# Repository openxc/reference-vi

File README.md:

OpenXC Vehicle Interface Reference Design
=========================================

This repository is a part of the [OpenXC][] project.

This repository contains the documentation and open source design files for the
OpenXC vehicle interface reference design, originally created by Ford.

## Documentation

The documentation is in the form of simple website, written in Markdown with the
HTML generated with [Jekyll][jekyll].

[jekyll]: http://jekyllrb.com/

### Organization

* the `*.mkd` files are the source for the documentation website - they're very
  readable as plain text files, too, if you're just digging through the
  repository.
* `static/` contains the static JavaScript, CSS and images for the site.
* `_layouts/default.html` contains the main layout for the site. There's only 1
  layout for now, although there could others in the future.
* `electrical/` contains the electrical design files and documentation.
* `mechanical/` contains the mechanical housing design files and documentation.
* `assembly/` contains documentation to support final assembly at a fabrication
  house.

### Local development

If you do not have ruby and RubyGems installed (you already do on OS X), see
below.

Assuming you have Ruby and RubyGems installed:

    $ gem install rdiscount jekyll

Then, assuming you have Python's `pip` installed:

    $ pip install pygments

Then run the local development server:

    $ cd reference-vi
    reference-vi/ $ jekyll serve -w

and point your browser to http://localhost:4000.

Jekyll uses the templates in the repository to generate a static html version of
the site. The static version is always dumped in the `_site` subdirectory in the
repository - this is *not* committed, since it's automatically generated. The
`-w` flag turns on auto-recompilation, so anytime you change a file it will
regenerate whatever files have changed, so you just need to refresh the browser
to see your latest updates.

### Installing Ruby and RubyGems

**Cygwin in Windows**

TODO is this necessary anymore?

Install the `ruby`, `make`, `gcc`, `libiconv` and `zlib` packages in
Cygwin using the `setup.exe`
you downloaded earlier. Download the RubyGems TGZ package from
http://rubygems.org/pages/download and put it in `C:\cygwin\home\<your
username>`. Fire up Cygwin and run this:

    $ tar -xzf rubygems*.tgz
    $ cd rubygems*
    $ ruby setup.rb

Jekyll depends on posix-spawn v0.3.6, but that has a problem with compiling in
Cygwin. The latest development version works, though, so install that gem from
source before continuing:

    $ git clone https://github.com/rtomayko/posix-spawn.git
    $ cd posix-spawn
    $ gem build posix-spawn.gemspec
    $ gem install posix-spawn-0.3.6.gem

If you didn't get any errors, return to the top of this section and install
jekyll.

### Going Live

The documentation site is hosted on GitHub pages, so deploying is as simple as
commiting your changes to the `gh-pages` branch and pushing to GitHub. It gets
regenerated within a minute or two, and then it's live. This of course means
don't push anything in the `gh-pages` branch that isn't 100% done!

## License

Copyright (c) 2013 Ford Motor Company

The electrical and mechanical designs in this repository are available under the
[Creative Commons Attribution 4.0
International](http://creativecommons.org/licenses/by/4.0/deed.en_US) license.

[OpenXC]: http://openxcplatform.com

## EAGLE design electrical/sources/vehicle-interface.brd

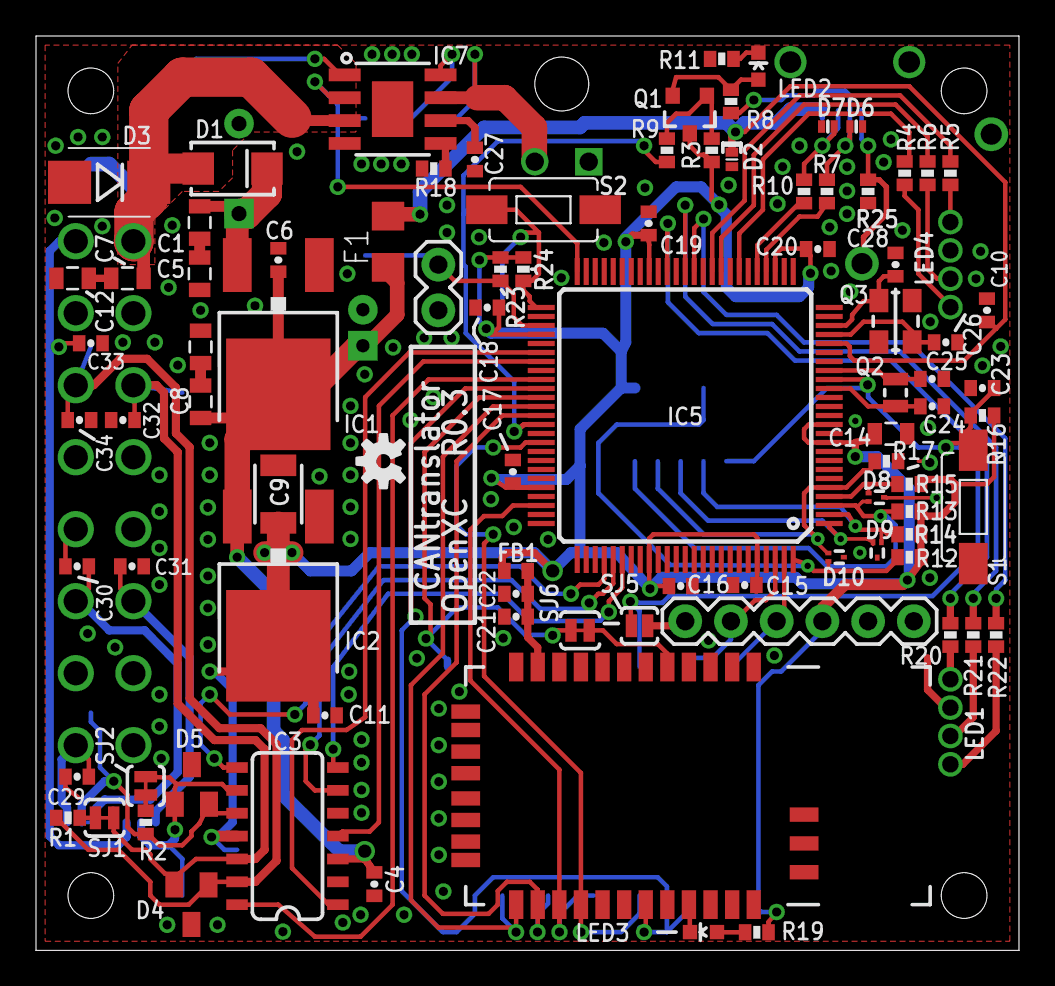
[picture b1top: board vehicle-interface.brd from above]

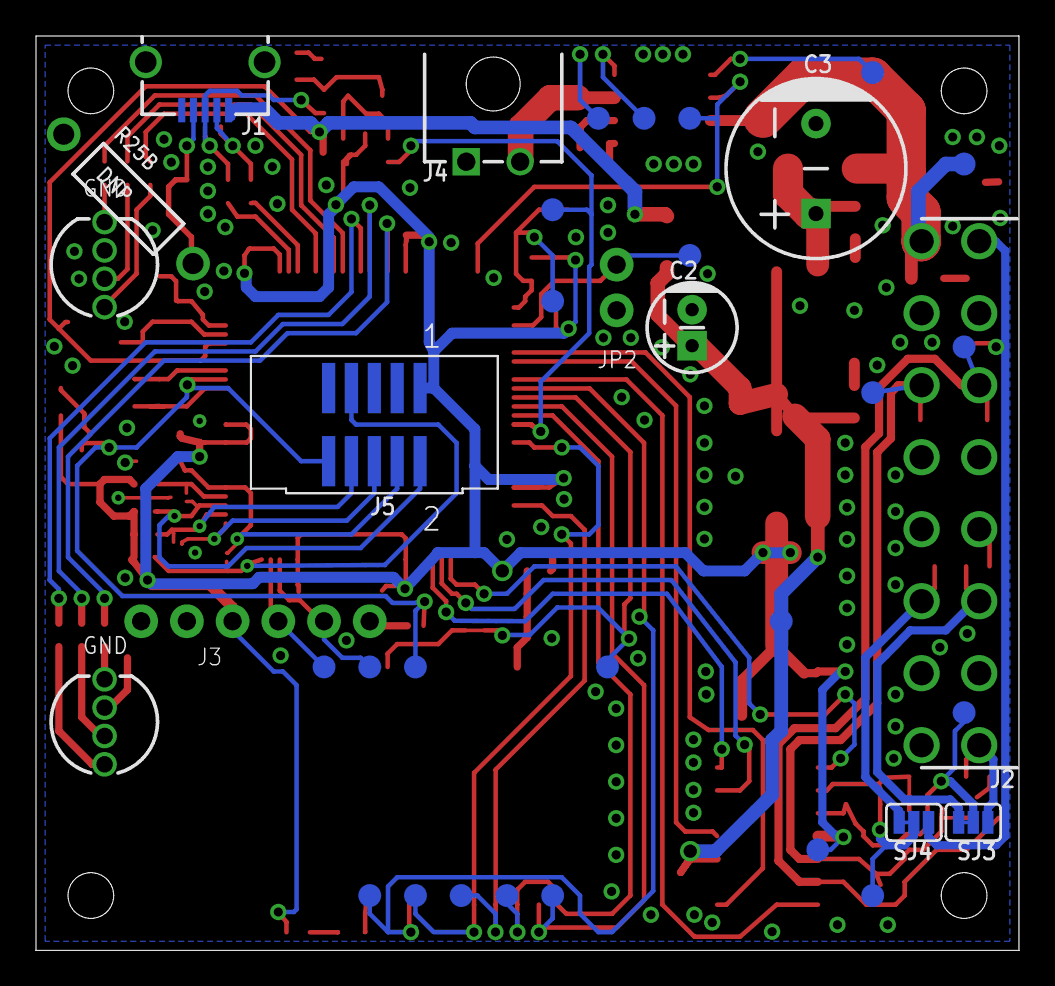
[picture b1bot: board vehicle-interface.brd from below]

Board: 2 copper layers, 54.6 x 50.8 mm, 125 parts (34 on the bottom side), 76 nets.

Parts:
C1, C5, C8, C13: 0.1u; 0805
C2: 150u; CPOL-5MMX2D
C3: 270u; CPOL-10MMX5D
C4, C11: 22n; 0402-CAP
C6, C10, C15, C16, C17, C18, C19, C20, C21, C23: 0.1u; 0402-CAP
C7, C12: 0.47u; 0805
C9: 47u; 1210
C14: 10u; 0805
C22, C27: 1u; 0402-CAP
C24, C25, C26, C28: 18p; 0402-CAP
C29, C30, C31, C32, C33, C34: 100p; 0402-CAP
D1: RS1J; SMA-DIODE
D2: PESD12VS1ULD; SOD-882D
D3: 1SMB16CAT3G; SMB-DIODE
D4, D5: PESD1CAN; SOT23
D6, D7: PESD5V0X1BL; SOD-882
D8, D9, D10: SOT-1123
DRILEGEND: DRILEGEND
F1: MF-MSMF110/16-2; R1206
F2: OSHW-LOGO-S
FB1: 742843122; C0402
IC1: LM340S-50; V-REG_DPACK
IC2: TLE4284DV33; V-REG_DPACK
IC3: TJA1048T; SO14
IC5: LPC1769FBD100; TQFP100
IC6: RN41-I/RM; RN41
IC7: TPS2421-2; POWER_SO8
J1: USB_MINIB_SHIELD-10118193; 10118193
J2: OBDII; OBDII-COMTECH
J3: ISP; 1X06
J4: PWR OUT; 2-1445055-2
J5: ARM mini-JTAG; SHF-105-01-X-D-SM
JP2: ISP_EN; 1X02
LED1, LED4: RGB; LED5MM-RGB
LED2, LED3: SML-LX0603SRW; LED-0603
Q1: BC856; SOT23-3
Q2: 32k; ST2012SB
Q3: 12M; CX3225SB
R1, R2, R25: 120; 0402-RES
R3, R12, R13, R14, R16, R17, R23, R24: 10k; 0402-RES
R4, R22: 17.4; 0402-RES
R5, R20: 143; 0402-RES
R6, R21: 30; 0402-RES
R7, R10: 33E; 0402-RES
R8: 1.5k; 0402-RES
R9: 2k; 0402-RES
R11, R19: 560; 0402-RES
R15: 4.7k; 0402-RES
R18: 49.9k; 0402-RES
R25B: DNP; AXIAL-0.4
S1: RESET; TACTILE-SWITCH-1101NE
S2: PROG; TACTILE-SWITCH-1101NE
SJ1, SJ2, SJ6: CLOSED; SJ_2S-TRACE
SJ3, SJ4: SJ_3_PASTE1&2
SJ5: OPEN; SJ_2S-NO
TP1, TP2, TP3, TP4, TP5, TP6, TP7, TP8, TP9, TP10, TP11, TP12, TP13, TP14, TP15, TP16, TP17, TP18, TP19, TP20, TP21, TP22, TP23: PAD.03X.05
ZDRAW1: A4L-LOC

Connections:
3.3V: C9.1, C11.1, C14.1, C15.1, C16.1, C17.1, C18.1, C19.1, C20.1, FB1.2, IC2.4, IC3.11, IC5.10, IC5.12, IC5.28, IC5.42, IC5.54, IC5.71, IC5.84, IC5.96, J3.4, J5.1, Q1.3, R3.2, R12.1, R13.1, R14.1, R15.1, R16.2, R19.1, R23.1, R24.1, TP7.P$1
5V: C2.1, C4.1, C6.2, C8.1, F1.1, IC1.4, IC2.3, IC3.3, TP6.P$1
!BT_RST: IC5.61, SJ6.1, TP12.P$1
!ISP_EN: IC5.53, JP2.1, R23.2, TP17.P$1
!RESET: C23.1, IC5.17, J5.10, R16.1, S1.P$2, SJ5.1, TP21.P$1
!USBBOOT_EN: IC5.51, R24.2, S2.P$2, TP18.P$1
+12V: C7.1, D1.A, D3.C, IC7.3, J2.16, TP5.P$1
BT_CONN: IC5.60, IC6.19, TP13.P$1
BT_CTS: IC5.66, IC6.16, TP11.P$1
BT_RTS: IC5.73, IC6.15, TP10.P$1
BT_RX: IC5.62, IC6.13, TP8.P$1
BT_TX: IC5.63, IC6.14, TP9.P$1
CANA_EN: IC3.14, IC5.59
CANA_RX: IC3.4, IC5.57
CANA_TX: IC3.1, IC5.56
CANB_EN: IC3.8, IC5.79
CANB_RX: IC3.7, IC5.81
CANB_TX: IC3.6, IC5.80
DEBUG_RX: IC5.99, J3.3, TP20.P$1
DEBUG_TX: IC5.98, J3.2, TP19.P$1
GND: C2.2, C3.1, C4.2, C5.2, C6.1, C9.2, C10.2, C11.2, C12.2, C13.2, C14.2, C15.2, C16.2, C17.2, C18.2, C19.2, C20.2, C21.1, C22.1, C23.2, C24.1, C25.1, C26.2, C27.2, C28.2, C29.2, C30.2, C31.2, C32.2, C33.2, C34.2, D2.2, D3.A, D4.3, D5.3, D6.1, D7.1, D8.3, D9.3, D10.3, IC1.1, IC2.1, IC3.2, IC3.5, IC5.11, IC5.15, IC5.31, IC5.41, IC5.55, IC5.72, IC5.83, IC5.97, IC6.1, IC6.12, IC6.25, IC6.27, IC6.28, IC6.29, IC7.4, IC7.PAD, J1.5, J1.S1, J1.S2, J2.4, J2.5, J3.6, J4.1, J5.3, J5.5, J5.9, JP2.2, LED1.2, LED4.2, R11.1, R17.2, R18.2, R25.1, R25B.P$1, S1.P$1, S2.P$1
HSPD_HI: C34.1, D4.1, IC3.13, J2.6, R1.1, TP1.P$1
HSPD_LO: C32.1, D4.2, IC3.12, J2.14, SJ1.1, TP2.P$1
MSPD_HI: C30.1, D5.2, IC3.10, J2.3, R2.2, SJ3.1, SJ3.2, TP3.P$1
MSPD_LO: C31.1, D5.1, IC3.9, J2.11, SJ2.2, SJ4.1, SJ4.2, TP4.P$1
MULTI_HI: C29.1, J2.1, SJ3.3
MULTI_LO: C33.1, J2.8, SJ4.3
unnamed: R1.2, SJ1.2
unnamed: IC5.40, R20.1
unnamed: R2.1, SJ2.1
unnamed: IC5.50, IC7.2, TP14.P$1
unnamed: LED1.4, R22.2
unnamed: IC6.21, LED3.C
unnamed: C7.2, C12.1
unnamed: LED3.A, R19.2
unnamed: IC5.38, R21.1
unnamed: IC5.37, R22.1
unnamed: LED1.3, R21.2
unnamed: LED1.1, R20.2
unnamed: IC7.5, R18.1
unnamed: C27.1, IC7.6
unnamed: LED4.4, R4.2
unnamed: IC5.32, R4.1
unnamed: C25.2, IC5.18, Q2.1
unnamed: C8.2, C13.1
unnamed: J1.4, R25.2, R25B.P$2
unnamed: D7.2, J1.2, R10.2
unnamed: C1.2, C5.1
unnamed: C1.1, C3.2, D1.C, IC1.3
unnamed: C24.2, IC5.16, Q2.2
unnamed: D6.2, J1.3, R7.2, R8.1
unnamed: C26.1, IC5.22, Q3.3
unnamed: C28.1, IC5.23, Q3.1
unnamed: LED2.A, Q1.2, R8.2
unnamed: LED2.C, R11.2
unnamed: Q1.1, R3.1, R9.1
unnamed: LED4.3, R6.2
unnamed: LED4.1, R5.2
unnamed: IC5.34, R6.1
unnamed: IC5.35, R5.1
unnamed: IC7.1, TP22.P$1
unnamed: IC7.8, TP23.P$1
unnamed: J3.1, SJ5.2
unnamed: IC6.5, SJ6.2
unnamed: C21.2, C22.2, FB1.1, IC6.11
RTCK: D10.2, IC5.100, J5.7, R12.2
TCK: D10.1, IC5.5, J5.4, R17.1
TDI: D9.1, IC5.2, J5.8, R14.2
TDO: D9.2, IC5.1, J5.6
TMS: D8.2, IC5.3, J5.2, R13.2
TRST: D8.1, IC5.4, R15.2
USB_CON: IC5.64, R9.2, TP16.P$1
USB_D+: IC5.29, R7.1
USB_D-: IC5.30, R10.1
USB_VBUS: C10.1, D2.1, F1.2, IC5.21, J1.1
VOUT: IC7.7, J4.2, TP15.P$1

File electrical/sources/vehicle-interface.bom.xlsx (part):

Part | Value | Package | Manu | Part # | Volt/Precision | Other | Link | Cost/1k
C1 | 0.1u | CAP0805 | Kemet | C0805C104K5RACAUTO | X7R | 50V | http://ca.mouser.com/ProductDetail/Kemet/C0805C104K5RACAUTO/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 | 2.7E-2
C2 | 150u | CAP_POL5MMX2D | Panasonic | EEU-FR1A151B | 0.2 | 10V | http://ca.mouser.com/ProductDetail/Panasonic-Electronic-Comp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 | 6.4000000000000001E-2
C3 | 270u | CAP_POL10MMX5D | Panasonic | EEU-FR1V271 | 0.2 | 35V | http://www.digikey.com/product-detail/en/EEU-FR1V271/P14438-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 | 0.214
C4 | 22n | CAP0402-CAP | Murata | GCM155R71H223KA55D | X7R | 16V | http://ca.mouser.com/ProductDetail/Murata/GCM155R71H223KA55D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 | 1.6E-2 |  | Change to 0603 package
C5 | 0.1u | CAP0805 | Kemet | C0805C104K5RACAUTO | X7R | 50V | http://ca.mouser.com/ProductDetail/Kemet/C0805C104K5RACAUTO/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 | 2.7E-2
C6 | 0.1u | CAP0402-CAP | Murata | GRM155R71C104JA88D | X7R | 16V | http://ca.mouser.com/ProductDetail/Murata/GRM155R71C104JA88D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 | 7.0000000000000001E-3 |  | Change to 0603 package
C7 | 0.47u | CAP0805 | Kemet | C0805C474K5RACTU | X7R | 50V | http://ca.mouser.com/ProductDetail/Kemet/C0805C474K5RACTU/?q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 | 6.3E-2
C8 | 0.1u | CAP0805 | Kemet | C0805C104K5RACAUTO | X7R | 50V | http://ca.mouser.com/ProductDetail/Kemet/C0805C104K5RACAUTO/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 | 2.7E-2
C9 | 47u | CAP1210 | Murata | GRM32ER71A476KE15L | X7R | 10V | http://ca.mouser.com/ProductDetail/Murata/GRM32ER71A476KE15L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 | 0.72199999999999998
C10 | 0.1u | CAP0402-CAP | Murata | GRM155R71C104JA88D | X7R | 16V | http://ca.mouser.com/ProductDetail/Murata/GRM155R71C104JA88D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 | 7.0000000000000001E-3 |  | Change to 0603 package
C11 | 22n | CAP0402-CAP | Murata | GCM155R71H223KA55D | X7R | 16V | http://ca.mouser.com/ProductDetail/Murata/GCM155R71H223KA55D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 | 1.6E-2 |  | Change to 0603 package
C12 | 0.47u | CAP0805 | Kemet | C0805C474K5RACTU | X7R | 50V | http://ca.mouser.com/ProductDetail/Kemet/C0805C474K5RACTU/?q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 | 6.3E-2
C13 | 0.1u | CAP0805 | Kemet | C0805C104K5RACAUTO | X7R | 50V | http://ca.mouser.com/ProductDetail/Kemet/C0805C104K5RACAUTO/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 | 2.7E-2
C14 | 10u | CAP0805 | Kemet | C0805C106K8RACTU | X7R | 10V | http://ca.mouser.com/ProductDetail/Kemet/C0805C106K8RACTU/?q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 | 0.14799999999999999
C15 | 0.1u | CAP0402-CAP | Murata | GRM155R71C104JA88D | X7R | 16V | http://ca.mouser.com/ProductDetail/Murata/GRM155R71C104JA88D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 | 7.0000000000000001E-3 |  | Change to 0603 package
C16 | 0.1u | CAP0402-CAP | Murata | GRM155R71C104JA88D | X7R | 16V | http://ca.mouser.com/ProductDetail/Murata/GRM155R71C104JA88D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 | 7.0000000000000001E-3 |  | Change to 0603 package
C17 | 0.1u | CAP0402-CAP | Murata | GRM155R71C104JA88D | X7R | 16V | http://ca.mouser.com/ProductDetail/Murata/GRM155R71C104JA88D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 | 7.0000000000000001E-3 |  | Change to 0603 package
C18 | 0.1u | CAP0402-CAP | Murata | GRM155R71C104JA88D | X7R | 16V | http://ca.mouser.com/ProductDetail/Murata/GRM155R71C104JA88D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 | 7.0000000000000001E-3 |  | Change to 0603 package
C19 | 0.1u | CAP0402-CAP | Murata | GRM155R71C104JA88D | X7R | 16V | http://ca.mouser.com/ProductDetail/Murata/GRM155R71C104JA88D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 | 7.0000000000000001E-3 |  | Change to 0603 package
C20 | 0.1u | CAP0402-CAP | Murata | GRM155R71C104JA88D | X7R | 16V | http://ca.mouser.com/ProductDetail/Murata/GRM155R71C104JA88D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 | 7.0000000000000001E-3 |  | Change to 0603 package
C21 | 0.1u | CAP0402-CAP | Murata | GRM155R71C104JA88D | X7R | 16V | http://ca.mouser.com/ProductDetail/Murata/GRM155R71C104JA88D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 | 7.0000000000000001E-3 |  | Change to 0603 package
C22 | 1u | CAP0402-CAP | Murata | GRM155R60J105KE19D | X5R | 6.3V | http://ca.mouser.com/ProductDetail/Murata/GRM155R60J105KE19D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 | 1.3000000000000001E-2 |  | Change to 0603 package
C23 | 0.1u | CAP0402-CAP | Murata | GRM155R71C104JA88D | X7R | 16V | http://ca.mouser.com/ProductDetail/Murata/GRM155R71C104JA88D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 | 7.0000000000000001E-3 |  | Change to 0603 package
C24 | 18p | CAP0402-CAP | Murata | GRM1555C1H180JA01D | C0G | 50V | http://ca.mouser.com/ProductDetail/Murata/GRM1555C1H180JA01D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 | 7.0000000000000001E-3 |  | Change to 0603 package
C25 | 18p | CAP0402-CAP | Murata | GRM1555C1H180JA01D | C0G | 50V | http://ca.mouser.com/ProductDetail/Murata/GRM1555C1H180JA01D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 | 7.0000000000000001E-3 |  | Change to 0603 package
C26 | 18p | CAP0402-CAP | Murata | GRM1555C1H180JA01D | C0G | 50V | http://ca.mouser.com/ProductDetail/Murata/GRM1555C1H180JA01D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 | 7.0000000000000001E-3 |  | Change to 0603 package
C27 | 1u | CAP0402-CAP | Murata | GRM155R60J105KE19D | X5R | 6.3V | http://ca.mouser.com/ProductDetail/Murata/GRM155R60J105KE19D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 | 1.3000000000000001E-2 |  | Change to 0603 package
C28 | 18p | CAP0402-CAP | Murata | GRM1555C1H180JA01D | C0G | 50V | http://ca.mouser.com/ProductDetail/Murata/GRM1555C1H180JA01D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 | 7.0000000000000001E-3 |  | Change to 0603 package
C29 | 100p | CAP0402-CAP | Murata | GRM1557U1H101JZ01D | U2J | 50V | http://ca.mouser.com/ProductDetail/Murata/GRM1557U1H101JZ01D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 | 2.6000000000000002E-2 |  | Change to 0603 package
C30 | 100p | CAP0402-CAP | Murata | GRM1557U1H101JZ01D | U2J | 50V | http://ca.mouser.com/ProductDetail/Murata/GRM1557U1H101JZ01D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 | 2.6000000000000002E-2 |  | Change to 0603 package
C31 | 100p | CAP0402-CAP | Murata | GRM1557U1H101JZ01D | U2J | 50V | http://ca.mouser.com/ProductDetail/Murata/GRM1557U1H101JZ01D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 | 2.6000000000000002E-2 |  | Change to 0603 package
C32 | 100p | CAP0402-CAP | Murata | GRM1557U1H101JZ01D | U2J | 50V | http://ca.mouser.com/ProductDetail/Murata/GRM1557U1H101JZ01D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 | 2.6000000000000002E-2 |  | Change to 0603 package
C33 | 100p | CAP0402-CAP | Murata | GRM1557U1H101JZ01D | U2J | 50V | http://ca.mouser.com/ProductDetail/Murata/GRM1557U1H101JZ01D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 | 2.6000000000000002E-2 |  | Change to 0603 package
C34 | 100p | CAP0402-CAP | Murata | GRM1557U1H101JZ01D | U2J | 50V | http://ca.mouser.com/ProductDetail/Murata/GRM1557U1H101JZ01D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 | 2.6000000000000002E-2 |  | Change to 0603 package
D1 | RS1J | DIODESMA | Vishay | RS1J-E3/5AT | 1A | 600V | http://ca.mouser.com/ProductDetail/Vishay-Semiconductors/RS1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 | 0.11900000000000001
D2 | PESD12VS1ULD | SOD-882D | NXP | PESD12VS1ULD,315 | 12V | 150W | http://ca.mouser.com/ProductDetail/NXP/PESD12VS1ULD315/?qs=%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 | 0.10200000000000001
D3 | 1SMB16CAT3G | DIODE-TVS-SMB | ON Semi | 1SMB16CAT3G | 16V | 600W | http://ca.mouser.com/ProductDetail/ON-Semiconductor/1SMB16CA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 | 0.155
D4 | PESD1CAN | DIODE_ESD_DUAL-SOT-23 | NXP | PESD1CAN,215 | 40V | 200W | http://ca.mouser.com/ProductDetail/NXP/PESD1CAN215/?qs=%2fha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 | 8.3000000000000004E-2
D5 | PESD1CAN | DIODE_ESD_DUAL-SOT-23 | NXP | PESD1CAN,215 | 40V | 200W | http://ca.mouser.com/ProductDetail/NXP/PESD1CAN215/?qs=%2fha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 | 8.3000000000000004E-2
D6 | PESD5V0X1BL | SOD-882 | NXP | PESD5V0X1BL,315 | 5V | 9kV | http://ca.mouser.com/ProductDetail/NXP/PESD5V0X1BL315/?qs=%2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 | 0.22
D7 | PESD5V0X1BL | SOD-882 | NXP | PESD5V0X1BL,315 | 5V | 9kV | http://ca.mouser.com/ProductDetail/NXP/PESD5V0X1BL315/?qs=%2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 | 0.22
D8 | ESD11A3.3 | SOT-1123 | On Semi | ESD11A3.3DT5G | 5.2V | 16kV | http://ca.mouser.com/ProductDetail/ON-Semiconductor/ESD11A33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 | 0.113
D9 | ESD11A3.3 | SOT-1123 | On Semi | ESD11A3.3DT5G | 5.2V | 16kV | http://ca.mouser.com/ProductDetail/ON-Semiconductor/ESD11A33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 | 0.113
D10 | ESD11A3.3 | SOT-1123 | On Semi | ESD11A3.3DT5G | 5.2V | 16kV | http://ca.mouser.com/ProductDetail/ON-Semiconductor/ESD11A33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 | 0.113
F1 | MF-MSMF110/16-2 | PTCFUSE-1206 | Bourns | MF-MSMF110/16-2 | 16V | 1.1A | http://ca.mouser.com/ProductDetail/Bourns/MF-MSMF110-16-2/?q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 | 0.34200000000000003
FB1 | 742843122 | C0402 | Wurth | 742843122 | 1GHz | 0.5A | http://ca.mouser.com/ProductDetail/Wurth-Electronics/7428431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 | 0.16900000000000001
IC1 | TLE4284DV50 | V_REG_317DPACK | Infineon | TLE4284D V50 | 5V | 1.6A | http://www.digikey.com/product-detail/en/TLE4284D%20V50/TLE4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 | 0.97499999999999998
IC2 | TLE4284DV33 | V_REG_317DPACK | Infineon | TLE4284D V33 | 3.3V | 1.6A | http://www.digikey.ca/product-detail/en/TLE4284D%20V33/TLE42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 | 1.0249999999999999
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
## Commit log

2013-04-19 Initial commit.
2013-04-19 Add .gitingore for Eagle backup files.
2013-04-19 Change name to "Vehicle Interface" and "VI".
2013-05-28 Fix docs for when termination resistors should be used.
2013-05-28 Adding updating enclosure files
2013-08-08 Inital commit with jekyll site skeleton.
2013-08-27 Rename CAN translator -> vehicle interface.
2013-09-11 Use "v" as version prefix instead of "R" for revision.
2013-09-17 Re-link images with proper names.
2013-09-17 Add license and update main README.
2013-09-17 Add jekyll instructions to the README.
2013-09-17 Collect static files for docs to make organization clearer.
2013-09-17 Re-organize the files a bit.
2013-09-17 Move assembly docs to the new location.
2013-09-17 Split up remaining README files.
2013-09-17 Oragnize remaining files from docs directory.
2013-09-18 Add design critera directly to HTML, not as an Excel file.
2013-09-18 Add cost optimization ideas.
2013-09-18 Add notes from Zac on DFM for the housing.
2013-09-18 Move BT testing images to testing folder.
2013-09-18 Add more notes on power supply schematic.
2013-09-18 Add high level design requirements.
2013-09-18 Add final production version of housing design.
2013-09-18 Add latest version of BOM.
2013-09-18 Remove software license - there is no code in this repo now.
2013-09-18 Update CNAMEUpdate CNAME..
2013-09-18 Add notes from pitch document.
2013-09-18 Add title next to logo.
2013-09-18 Add a link back to openxcplatform.com in the top right corner.
2013-09-18 Organize to match new site structure ideas.
2013-09-18 Update to Bootstrap 2.3.2.
2013-09-18 Shrink the top links.
2013-09-18 Add sub-nav to each section.
2013-09-19 Add quick start info for 3 developer demographics.
2013-09-19 Review the entire site, mark all remaining TODOs.
2013-09-19 Link to AUTHORS file from index.
2013-09-19 Add new images of VI closer to production version.
2013-09-19 Add preview images of board layout and schematic.
2013-09-19 Add images for firmware flashing instructions.
2013-09-19 Add image of JTAG header.
2013-09-19 Add ISP header image.
2013-09-19 Explain that RN-41 setup isn't required with official firmware.
2013-09-19 Give a very high level description of how to get this made.
2013-09-19 Add missing image.
2013-09-19 Fix display of bluetooth testing results.
2013-09-19 Add a simple diagram of ports on VI.
2013-09-20 Move images around on index.
2013-09-20 Proofread a few sections and add new top/bottom PCB diagrams.
2013-09-20 Final proof read before releasing draft.
2013-09-20 Highlight Overview nav button when on index page.
2013-09-20 Add GitHub Fork button to top nav.
2013-09-20 Update to Bootstrap 3.0.
    Fixed #7.
2013-09-20 Add links to new starter firmware project.
2013-09-23 Edits to the main page, including adding Zac as a technical contributor.
2013-09-23 Correct Zac's email
2013-09-23 Correct language around CAN transceiver.
2013-09-23 Clean up some of the requirements language, ref RN-41 not 42.
2013-09-23 Remove reference to the Dock
2013-09-23 Remove references to the Dock, correct capitalization.
2013-09-23 Fix capitalization, typos, remove references to Ford approval.
2013-09-23 Correct Protomold's name.
2013-09-23 Fix broken RN-41 link.
2013-09-23 Correct LPC model number
2013-09-23 Switch USB docs back to looking for 'LPC1759'
    The bootloader actually does say LPC1759 since it was originally designed for that, and I never did change that before the production run.
2013-09-24 Match CNAME to that in the prototype VI box literature.
2013-09-24 Be clear that we meet electrical requirements.
    Fixed #13.
2013-09-24 Add CLI flashing docs for Windows and Mac.
2013-09-24 Grab jQuery from Google instead of jQuery's CDN for speed.
2013-09-24 Add more details to the firmware index page.
    Fixed #18.
2013-10-02 Note that termination resistor functionality is reversed.
2013-10-07 Mention that some vehicle may need an extension cable.
    Fixed #17.
2013-10-07 Add an image of the VI installed in a car.
    Fixed #19.
2013-10-07 Mention version of shipping PCB.
    Fixed #20.
2013-10-07 Update all images to show shipping housing and PCB.
    I didn't change some of the heavily marked up images as the only change
    to the PCB is the OBD-II connector - we'll see if anyone notices.
    Fixed #22.
2013-10-08 Add link to request form.
2013-10-13 Update GA tracking to show up as a subdomain.
2013-10-17 Fix link in CAN docs.
2013-10-21 Update VI testing links.
2013-11-01 Fix link to BOM.
2013-11-19 Add a link to physical fit wiki page.
2013-12-05 Fix styles in IE8.
    Fixed #24.
2013-12-17 Add nav toggle button for narrow screens.
2014-01-28 Update license to CC 4.0 International.
2014-02-14 Don't use markdown in HTML blocks.
2014-02-14 Make Linux programming instructions more explicit.
2014-02-14 Clarify statement about USB bootloader.
2014-02-14 Remove extra trailing slash.
2014-03-05 Add instructions for v1.1 bootloader.
2014-03-12 Rank the complexity of different code options for VI.
2014-07-11 Fix typo.
2014-07-20 Update to new version of Google Analytics.
2014-09-04 update OBD-II connector info.
2014-10-06 updated bom
2014-12-22 updated engineering drawings and new BOM
2014-12-22 updated CAD files
2015-01-16 clarify: firmware.bin is a placeholder on the LPC1759 drive when programming.
2015-02-03 updated link for BOM
2015-02-03 updated mechanical section with 2D engineering drawing and step file
2015-02-03 corrected typo in BOM link
2015-02-03 Remove and ignore .DS_Store files from OS X.
2015-02-11 added bootloader hex file for ISP
2015-02-19 added ISP programming info
2015-02-25 updated pictures, added DFM info for mechanical and electrical
2015-02-25 updated factory testing plan
2015-02-25 updated gerber files, updated silkscreen for JP2 and J3 and GND polarity for LED1 and LED4
2015-02-26 updated the file extension for vistatic/images/-open.jpg
2015-10-15 remove original power schematic per request from Kevin & Karl.
2020-09-03 update multiple broken links.
2020-09-03 update to sizing for two images.
2020-09-09 fix photos on index page.
2020-09-09 update picture styling to fit page.
2020-09-09 markdown image resize attempt.
2020-09-09 attempt to resize markdown images with css.
2020-09-09 update markdown format for openxcplatform link.
2020-09-09 fix downmark formart for two links.
2020-09-09 update host device link and remove submit link because it is not supported anymore.
2020-09-10 fixed one more broken markdown link for openxcplatform website.
2020-09-10 fix 3 image links on mechanical page.
2020-09-10 Adjust image size.
2020-09-10 fix two more broken images links.
2020-11-23 remove a few mentions of bootloader 1.0 and attempting to fix markdown format.
2020-11-23 Testing markdown format in github.
2020-11-23 testing markdown format.
2020-11-23 testing html format.
2020-11-23 fix broken markdown format by replacing it with html.
2020-11-23 Remove old markdown dynamic hyperlinks.
2020-11-23 Remove divs.
2020-11-23 Return divs so tabs can work on the page.
2020-11-23 Test fix for div format.
2020-11-23 Test format fix for divs.
2020-11-23 Add fix for div format.
2020-11-23 Attempt to fix div formatting.
2020-11-23 Fix format for images.
2020-11-23 Fix code format.

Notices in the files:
parts and their libraries:
SparkFun-Passives: Licensing: CC v3.0 Share-Alike You are welcome to use this library for commercial purposes.
